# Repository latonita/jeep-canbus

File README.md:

# jeep-canbus   

Projects around CAN BUS in Chrysler Jeep - VES enabler, other small features

PCB for Aux + bluetooth based on xs3868 v3.0 added.

Here is CAN ID map I collected on CAN-B:

# Jeep Grand Cherokee WH 3.0 CRD - CAN-B — complete observed ID/byte map

This is the consolidated byte-level reference for every standard CAN ID that
actually occurs in the captures in this repository. Byte numbering is zero
based. Multi-byte integers are big-endian unless stated otherwise.

Confidence labels:

- **Confirmed** — controlled switch/action test or an unambiguous decode.
- **Probable** — strong behaviour and cross-log evidence; physical identity or
  scale is not completely calibrated.
- **Candidate** — useful working hypothesis that needs an external reference.
- **Unknown** — observed bytes/pattern only; no semantic claim.
- **Static/NM** — constant heartbeat or network-management traffic, not a
  vehicle measurement.

`FF`, a field of all `FF`, or `FFFFFF` frequently means unavailable during
wake-up/key-off. It is not a maximum physical reading.

## Vehicle, controls and measurements

| CAN ID | DLC / period | Byte and bit meaning | Confidence |
|---|---|---|---|
| `000` | 6 / 100 ms | `b0` ignition state: `00` wake/uninitialised, `01` off, `63` ACC, `85` ignition ON/running, `A9` crank. `b1..b5=00`. | **Confirmed** |
| `002` | 8 / 50 ms | `b0:b1` engine RPM, 1 rpm/count. `b2:b3` speed, raw/128 km/h. `b4:b5` wheel/distance pulse counter 1. `b6:b7` counter 2. Counters are rolling unsigned 16-bit values, about 25 counts/m. All `FF` = unavailable/engine off. They are distance pulses, **not wheel angles**. | **Confirmed** |
| `003` | 7 / ~450 ms | `b0` normally `00`; **`bit2`/`+04` = ESP/stability control switched off** (`04 21 80 01 50 FF 00` = Park with ESP off, 2026-10-13 stationary switch test). `b1` unknown (`00/01/05/0D/20/21` observed; constant `21` throughout the 2026-10-13 test). `b2` lever bitfield over a fixed `0x80`: `80=P`, `81=R`, `82=N`, `84=D` — **every AutoStick manual range also reads `84`**, so `b2` alone cannot separate D from a limited range. `b3 bit0` brake switch (`01` for the whole stationary shift test, foot on the brake). `b4` redundant PRNDL and the one byte that resolves the manual ranges — it is the **ASCII code of the character the cluster displays**: `50='P'`, `52='R'`, `4E='N'`, `44='D'`, `34='4'`, `33='3'`, `32='2'`, `31='1'` (AutoStick upper-limit ranges). `b5` normally `FF`. `b6 bit3` 4WD lever pulled; other bits unknown. | Gear/brake/4WD and ESP-off **confirmed**; `b4` ASCII encoding **confirmed**; `b1` unknown |
| `006` | 7 / 100 ms | `b0`: `00` key-off, `18` no indicator, `19` left, `1A` right, `1B` hazard; `38` also observed with an extra unknown bit. `b1..b6` are not decoded; common payloads include `22 04 00 00 02 58`, while the 2026 capture also has different `b1/b3/b4/b5` values. | Indicator byte **confirmed** |
| `013` | 5 / 500 ms | `b0 bit7` data-valid/module-awake; `b0 bit3=1` driver belt unbuckled. `b1=00`. `b2` door-ajar bits: bit0/`01` FL, bit1/`02` FR, bit2/`04` RR, bit3/`08` RL, bit4/`10` hatch; bits add. `b3:b4=49 99`. | **Confirmed** |
| `014` | 7 / 100 ms | `b0:b1:b2` 24-bit odometer, 0.1 km/count; `FFFFFF` unavailable. `b3=FF`. `b4` ambient/outside temperature in °C for the observed positive range: 2026 warm-weather drive `24→25`, older captures mostly `18` (`17–22` total). `b5` and `b6` remain unknown and are **not** validated as fuel level or economy. | Odometer **confirmed**; ambient **probable/high confidence**; `b5..b6` unknown |
| `015` | 6 / 100 ms | `b0` unknown temperature-like channel. `b1` battery/charging voltage in 0.1 V/count: `125` = 12.5 V key-on, `103` = 10.3 V cranking, `143–146` = 14.3–14.6 V running, and `126` = 12.6 V immediately after key-off. `b2` fast air-temperature channel, probably intake/charge air; its observed positive values read plausibly as raw °C, but identity and negative encoding are unconfirmed. `b3=FF`, `b4:b5=00`. | Voltage **confirmed/high confidence**; `b2` candidate; `b0` unknown |
| `01B` | 8 / ~100 ms | `b0` multiplex index `00/01/02`; `b1..b7` are seven ASCII VIN characters for that index. Concatenate the three indexed chunks and discard padding to obtain `1J8HCE8M45Y588369`. Index `03` with zeros appears during boot. | **Confirmed** |
| `02C` | 6 / ~500 ms in 2026 (~600 ms older captures) | `b0` engine-related analog strongly correlated with RPM (`r≈0.95`), possibly oil pressure or load. `b1` coolant temperature, `raw - 40` °C: the 2026 cold drive rises smoothly `68→132` (28→92 °C) in about 10 minutes, then holds `127–131` (87–91 °C); an independent 2015 cold start rises `65–70` to `126–128`. `b2` changing/load-related unknown analog. `b3` normally `64` (occasionally `63`); `b4:b5=00`. All `FF` means unavailable. | Coolant **high confidence**; scale **probable/high confidence**; `b0` candidate; `b2` unknown |
| `0D0` | 2 / ~1.15 s | `b0 bit7`/`+80` **parking brake engaged** — asserted for the first time in the 2026-10-13 stationary test (`04 00` released → `84 00` lever pulled). `b0 bit2`/`+04` was set throughout that session as the released-state baseline, while every 2015 capture reads a flat `00 00`; its meaning is unknown and it is not ESP-off (ESP was on for the `04 00` baseline). `b1=00` always. | Parking brake **confirmed**; `b0 bit2` unknown |
| `11D` | 3 / 100 ms | `b0` switch/button bitfield (`08/10/40` observed); exact button assignments unknown. `b1` small state `0..3`. `b2=00`. | **Unknown switch group** |
| `159` | 6 in every log / ~1 s (2026 drive n=1450: mean 1.0039 s, median 1.000 s, p5 0.998 s, p95 1.001 s; the sole 3.0 s gap is a pre-settling artefact between the first two frames) | `b0=FE` during normal running (100% of the 2026 drive log); power-up/power-down states also carry `00`, `04`, `05`, `0B` or `FF`. `b1:b3=FF FF FF` and DLC 6 are constant in every log in the repo. `b4` is a **validity flag**: `b4=00` ↔ `b5` is a real reading, `b4=01` ↔ `b5=0xFF` (unavailable), true with zero exceptions across every log — confirmed by two live transitions, `playback.log`'s ignition-off (`b4` flips to `01` and the frame settles permanently to `00 FF FF FF 01 FF`) and `radio-ignition-on`'s key-on (`05 FF FF FF 01 FF` → `05 FF FF FF 00 4D` the instant the key reaches ON). `b5` fuel level, probably **litres at 0.5 L/count**: the largest valid raw ever recorded is 154 (77.0 L) against this truck's 77.6 L/20.5 US gal tank — a percentage scale has no reason to stop at 154/255, a litre scale stops exactly where the tank does (`b5×0.5` and `b5/2.0` are the same transform; range alone cannot separate litres from percent, only this ceiling does). 2026 drive raw 138–142 = 69–71 L, logged the morning after a fill and matching the owner's "almost full" (the old `/2.55` percent conversion read the same fill as only 54%); hill trip 140→142 on the slope→138 at home = 70→71→69 L. Cross-check on older captures: raw 25–30 = 12.5–15.0 L (low fuel), raw 77 = 38.5 L (about half), raw 152–154 = 76–77 L (essentially full). Slosh is already heavily damped at the sender: every `b5` change in the 2026 drive is exactly ±1 count (30 changes, largest single step 0.5 L, full-trip peak-to-trough only 4 counts/2.0 L); a consumer could debounce changes shorter than ~10 s to remove the residual flip. Absolute calibration remains open — no brim-to-brim fill has been run against it. | Byte layout (`b4` validity flag, `b0` power-state variability) **confirmed** across every log in the repo; litre scale **probable** (capacity ceiling + owner cross-check), uncalibrated |
| `1A7` | 6 / 100 ms running, ~400 ms key-off | `Q=b0:b1` instantaneous fuel/injection flow; `FFFF` unavailable and zero is valid overrun cut. `b2..b5=00`. Integrate `Q×dt`; do not sum frames or multiply by RPM. Provisional scale: `flow_L/h=Q/160`, so `litres += Q×dt/(160×3600)`. | Rate identity **probable**; divisor 160 candidate |
| `1AC` | 1 / ~950 ms | `b0` dash/dome dimmer-wheel position: `01` top lock (dome on, instruments maximum), `02..08` descending brightness with dome off, `09` bottom lock (dome forced off, minimum). | **Confirmed** |
| `1B2` | 6 / ~1.45 s | `b0 bit7` 4WD lever pulled, causing blinking 4WD telltale/chime. `b1` observed `00/02/07`, probably transfer-case range/status but undecoded. `b2..b5=00`. | Lever bit **confirmed**; `b1` candidate |
| `1B4` | 6 (2953/2953) / 500 ms (mean 502.8 ms, median 500 ms, σ78 ms; 99.83% of gaps 480–520 ms) | `b0` 8-way direction enum: `0=N`, `1=NE`, `2=E`, `3=SE`, `4=S`, `5=SW`, `6=W`, `7=NW`, computed as `round(b1×2/45) mod 8` — sector centres sit at 0/45/90/.../315°, boundaries at 22.5/67.5/.../337.5°. A full 8-phase offset sweep confirms offset 0 with `round` (99.46% agreement, 2937/2953 frames) and rejects `floor` outright (best `floor` phase only 58.35%); independently cross-checked at 99.75% on a 1584-frame 2019 session. The 0.54% of disagreements are all boundary-quantization artifacts (e.g. `b1=146` → 292°, 0.5° shy of the 292.5° boundary, within the ±1° the 2°/count scale allows). `b1` magnetic heading in 2°/count (`0..179` → `0..358°`; observed range this session `0..178`, never reaching the documented 179 ceiling). `b2=07` constant in 2953/2953 frames, likely compass variance-zone/status — only its constancy is established, its meaning is not. `b3..b5=00` constant in 2953/2953 frames. A circular derivative of `b1×2` is only a coarse yaw-rate proxy. | Direction/heading **confirmed** against two independent sessions (2026 n=2953, 2019 n=1584); `b2` constancy **confirmed**, meaning still candidate |
| `1C8` | 1 / 500 ms | `b0` low bits: `00` exterior lights off, `01` position lamps, `02` low beam. Add bit4/`10` for front fog and bit5/`20` for rear fog: e.g. `12` low+front, `32` low+front+rear. | **Confirmed** |
| `210` | 2 / 500 ms | `b0`: `03` lights off, `02` any lights on; `00/01` occur as wake/key-off transients. `b1` instrument-panel dimmer: `00` with lights off; observed/hand-tested ladder `22/44/66/A4/C8`. | **Confirmed**, dimmer ladder one-note caveat |
| `2C0` | 8 / 100 ms | `b0:b1=FF FF`. `b2` accelerator pedal (23 rest, up to 234 floored in old capture). `b3≈b2/2`. `b4` unknown analog, about `7E` at rest. `b5=FF`. `b6` exact mirror of `b2`. `b7` status/validity flags (`02/0E/82/8E/...`). | Pedal **probable/high confidence**; flags unknown |
| `370` | 6 / event-driven | `b0` pulses `01` then `00`, one event per windscreen-wiper sweep. `b1..b5=00`. | **Confirmed** |

## RAR radio/head-unit IDs

The installed head unit is the **RAR radio**. The radio-unplug experiment
confirms that `09F`, `1AB`, `1BB`, `394`, `3D0` and NM node `416` belong to it.

| CAN ID | DLC / period | Byte and bit meaning | Confidence |
|---|---|---|---|
| `09F` | 8 / ~1 s | RAR radio source/current-mode state in `b0..b2`; exact value map incomplete. `b3=00`, `b4:b6=FF FF FF`, `b7=1F`. Closely mirrored by `394`. | Source **confirmed**, value map incomplete |
| `1AB` | 6 / ~3 s | Payload `03 00 00 00 00 00` in observed sessions. Head-unit heartbeat/status; individual semantics unknown. | Head unit **confirmed**; bytes unknown/static |
| `1BB` | 6 / ~1 s | `b0..b5=00` in all captures. Head-unit heartbeat/status. | Head unit **confirmed**; static |
| `394` | 6 / ~1 s | `b0..b2` mirror radio mode/status from `09F`. `b3` button bits: bit0 seek right, bit1 seek left, bit2 fast-forward, bit3 rewind, bit5 random/PTY. b4? `b5=00`. The head unit sends this frame **on press and again on release**, carrying the new state each time (owner, checked against the real unit) — so the ~1 s cadence is the idle heartbeat, not the report rate, and a short tap cannot fall between two frames. **No capture in this repository can confirm any of the bit or byte assignments: `b3`, `b4` and `b5` are all `0x00` in every one of the 5510 `394` frames logged, because nobody has ever pressed one of these buttons while recording.** The row said `b4` until the owner corrected it, and the logs were silent either way. | Byte/bit assignment **owner-stated, unconfirmed by any capture**; press/release behaviour **confirmed** |
| `3D0` | 7 / ~1 s | `b0` volume. `b1` bass, `b2` mid, `b3` treble, `b4` balance, `b5` fade; centre values are commonly around `0A` (fade observed `0C`). `b6=FF`. | **Confirmed/high confidence** |
| `3DD` | 8 / injected command | VES-present announcement to the RAR radio: `b0=03`, `b1..b7=00`. Transmitting `03 00 00 00 00 00 00 00` makes the RAR recognise VES as present and enables its AUX input. This was actively tested, not passively recorded. | **Confirmed by injection test** |

## Static, heartbeat and still-unknown cyclic IDs

These frames are retained because a complete map must show them, but a constant
payload is not proof of a physical meaning.

| CAN ID | DLC / period | Observed bytes | Confidence |
|---|---|---|---|
| `008` | 6 / ~1 s | `00 00 80 80 00 00`. | **Static/unknown** |
| `010` | 8 / ~2 s | Usually `41 01 15 71 63 80 2A 03`; `b0 bit1` participates in a shared alive/toggle burst (`41↔43`). | **Static/unknown** |
| `011` | 8 / ~2 s | Usually `3D 13 00 03 8B 40 00 00`; `b0 bit1` toggles (`3D↔3F`) with several related IDs. | **Static/unknown** |
| `012` | 6 / ~1 s | `b0=00`; `b1=00/10`; `b2=00/02/06`; `b3=40`; `b4:b5=0000/4999`. Possibly security/SKREEM-related, not established. | **Unknown** |
| `02E` | 2 / ~1 s | `1F 00`. | **Static/unknown** |
| `0EC` | 1 / ~1.5 s | `b0=00/01` toggle. | **Unknown** |
| `110` | 8 / ~3 s | Usually `95 7E 04 83 83 00 55 00`; `b0 bit1` toggles (`95↔97`) in the shared burst. | **Static/unknown** |
| `1AD` | 6 / ~2.7 s | Usually `01 42 42 04 01 00`; `b0 bit1` toggles (`01↔03`) in the shared burst. | **Static/unknown** |
| `1AE` | 6 / ~1.4 s | `00 00 00 00 00 00`. | **Static/unknown** |
| `1AF` | 8 / ~2.5 s | Usually `01 E7 00 40 01 A4 08 FF`; `b0 bit1` can toggle (`01↔03`) in the shared burst. | **Static/unknown** |
| `1B0` | 8 / ~5.4 s | `0D DE 03 E8 0A A0 08 DE`. | **Static/unknown** |
| `1B3` | 6 / ~2 s | `00 00 00 00 00 00`. | **Static/unknown** |
| `1B5` | 6 / ~6 s | `FD 0D 17 D1 00 00`. | **Static/unknown** |
| `1B6` | 7 / ~1 s | `00 18 FF 18 FF 18 FF`. | **Static/unknown** |
| `1F8` | 1 / ~2 s | `00`. | **Static/unknown** |
| `3A0` | 2 / 500 ms | `00 00`; heartbeat. | **Static** |
| `3F8` | 6 / 100 ms | `04 00 00 00 00 00`; fast heartbeat/reference frame. | **Static** |

The simultaneous `b0 bit1` changes in `010`, `011`, `110`, `1AD` and `1AF`
strongly suggest a shared transmitter/alive state. They do not establish what
the remaining payload fields mean.

## Rare/event-driven IDs with unknown function

| CAN ID | DLC | Observed bytes/behaviour | Confidence |
|---|---|---|---|
| `1E0` | 6 | Short burst with `b0=01`, ending in `b0=00`; `b1..b5=00`. | **Unknown event** |
| `1E2` | 6 | Rare event; `b0..b2` vary by session (`E4 0D D9`, `05 B7 6B`, `3D B4 65` observed); `b3..b5=00`. | **Unknown event** |
| `3F4` | 6 | Rare burst; `b0..b3` vary by session (`A5 1D E9 37`, `12 60 8F 55`, `28 8A A0 63` observed); `b4:b5=00`. | **Unknown event** |

## OSEK network-management ring

All seven frames have DLC 8 and recur about every 690 ms per node. They are
network management, not vehicle sensor data.

Common layout:

- `b0=FE`: node alive/announcing; `b1` is its own node address.
- `b0=FD`: ring/token data; `b1` is the next node address.
- `b2=3F` normally; bit7 gives `BF`, a sleep indication/request.
- `b3..b7=FF`.

| CAN ID | Node | Normal `FD` successor | Additional observation |
|---|---:|---:|---|
| `400` | `00` | `02` | NM node; module identity unknown. |
| `402` | `02` | `14` | NM node; module identity unknown. |
| `414` | `14` | `15` | NM node; module identity unknown. |
| `415` | `15` | `16` | NM node; module identity unknown. |
| `416` | `16` | `1C` | **RAR head unit/radio**, proven by unplug test. |
| `41C` | `1C` | `1E` | Joins the ring only while ignition is ON. |
| `41E` | `1E` | `00` | Often carries the sleep-indication bit in `b2`. |

The logical ring is `400 → 402 → 414 → 415 → 416 → 41C → 41E → 400`.

## Injected but not passively observed

`3DD` is a **confirmed VES-presence command** with payload
`03 00 00 00 00 00 00 00`: the RAR radio enables AUX when this frame is
transmitted. It never occurs naturally in the repository captures, so it
remains excluded from the 52 passively observed IDs.

## Important absences

- No direct steering-wheel or road-wheel angle has been identified.
- No accelerometer, pitch, roll or high-rate gyro/yaw signal has been identified.
- `1B4 b1` is compass heading and permits only a coarse derived yaw rate.
- `002 b4:b7` are wheel-pulse counters, not wheel angles.
- `1B4` carries no unavailable sentinel and does not stop at key-off: `b1=0xFF`
  is never observed across ~10 log files, and in `playback.log` the frame
  keeps transmitting at its normal cadence with an unchanged, valid heading
  (`06 85 07 00 00 00`, W/266°) straight through the `000` ignition-off
  transition and for ~1000 further lines until the capture ends. Anything
  consuming this must gate key-off on `000` or on bus silence, never on the
  compass frame itself (whether `1B4` eventually goes quiet on true bus sleep
  is unknown — the capture ends mid-stream).
- `159` is the mirror-image case: it does carry a real unavailable sentinel, in `b4`, and consumers must gate on it — `b4=01` means `b5=0xFF` is not a reading (let alone 100% full), true with no exceptions across every log in the repo.
- `1B4` heading is bit-for-bit static when stopped: across all 196
  consecutive stationary (≤2 km/h) sample pairs the 500 ms heading delta was
  exactly 0.0° (mean, median, max and stdev all zero) — no jitter to filter.
  Moving, the median 500 ms delta is 0° and mean |delta| is 1.9°; sustained
  turns run ~18–26°/s, with a genuine peak of 96° in one 500 ms sample
  (192°/s) at a hairpin apex on the hill switchbacks.

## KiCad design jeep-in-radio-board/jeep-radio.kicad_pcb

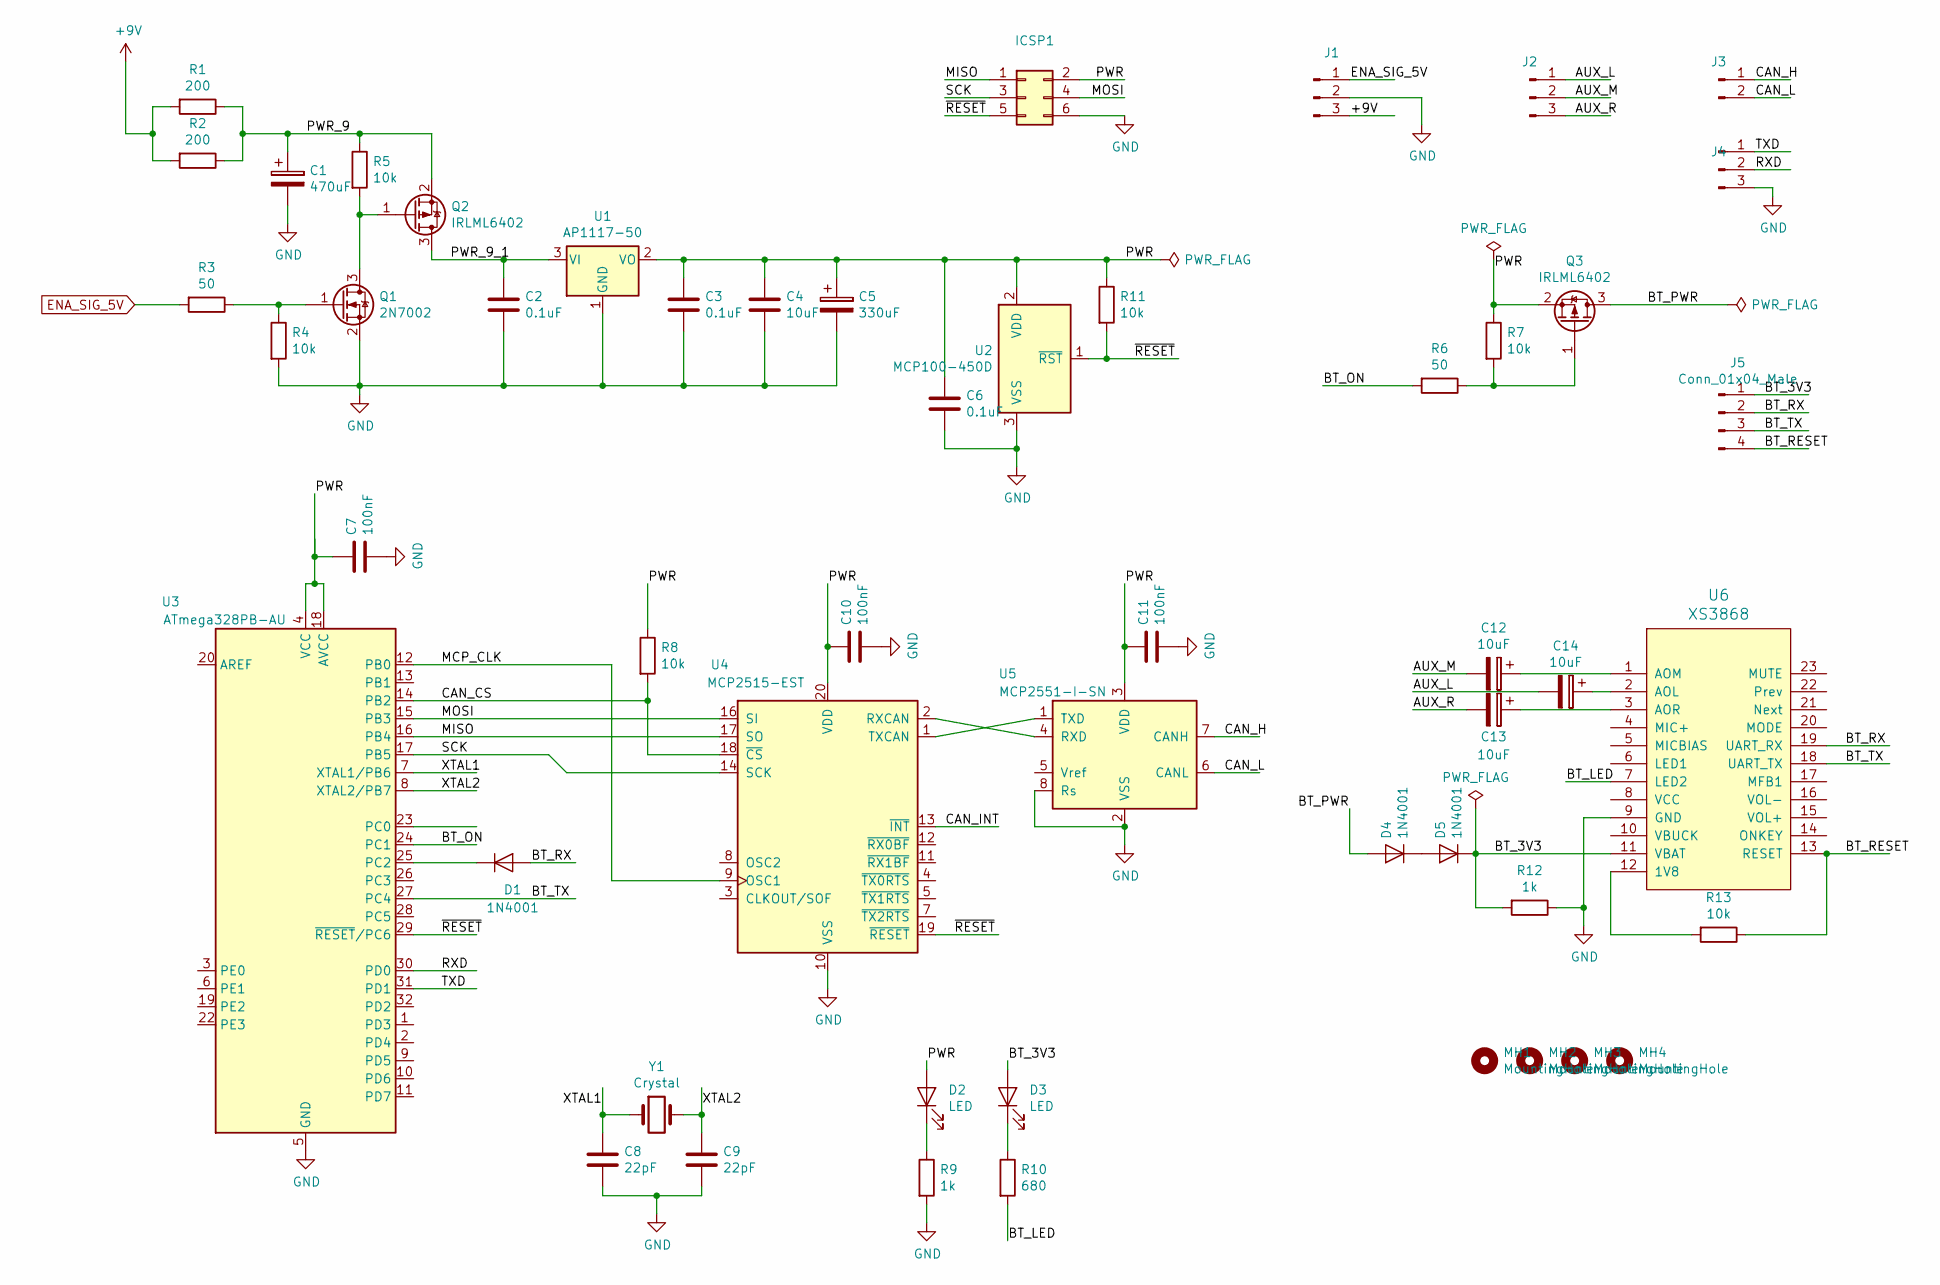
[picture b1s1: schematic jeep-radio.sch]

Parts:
C1: 470uF; CP_Radial_D8.0mm_P3.80mm
C2, C3, C6: 0.1uF; C_0805_2012Metric
C4: 10uF; CP_EIA-3216-18_Kemet-A
C5: 330uF; CP_Radial_D8.0mm_P3.80mm
C7, C10, C11: 100nF; C_0805_2012Metric
C8, C9: 22pF; C_0805_2012Metric
C12, C13, C14: 10uF; C_0805_2012Metric
D1, D4, D5: 1N4001; D_MELF
D2, D3: LED; LED_0603_1608Metric
ICSP1: Conn_02x03_Odd_Even; PinHeader_2x03_P2.54mm_Vertical
J1, J2, J4: Conn_01x03_Male; PinHeader_1x03_P2.54mm_Vertical
J3: Conn_01x02_Male; PinHeader_2x01_P2.54mm_Vertical
J5: Conn_01x04_Male; PinHeader_1x04_P2.54mm_Vertical
MH1, MH2, MH3, MH4: MountingHole; MountingHole_3.2mm_M3_DIN965
Q1: 2N7002; SOT-23
Q2, Q3: IRLML6402; SOT-23
R1, R2: 200; R_1206_3216Metric
R3, R6: 50; R_0805_2012Metric
R4, R5, R7, R8, R11, R13: 10k; R_0805_2012Metric
R9, R12: 1k; R_0805_2012Metric
R10: 680; R_0805_2012Metric
U1: AP1117-50; SOT-223-3_TabPin2
U2: MCP100-450D; SOT-23
U3: ATmega328PB-AU; TQFP-32_7x7mm_P0.8mm
U4: MCP2515-EST; TSSOP-20_4.4x6.5mm_P0.65mm
U5: MCP2551-I-SN; SOIC-8_3.9x4.9mm_P1.27mm
U6: XS3868
Y1: Crystal; Crystal_SMD_HC49-SD

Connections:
+9V: J1.3, R1.2, R2.2
/AUX_L: C14.2, J2.1
/AUX_M: C12.2, J2.2
/AUX_R: C13.2, J2.3
/BT_3V3: D3.2 (A), D5.1 (K), J5.1, R12.2, U6.11 (VBAT)
/BT_LED: R10.2, U6.7 (LED2)
/BT_ON: R6.2, U3.24 (PC1)
/BT_PWR: D4.2 (A), Q3.3 (D)
/BT_RESET: J5.4, R13.1, U6.13 (RESET)
/BT_RX: D1.2 (A), J5.2, U6.19 (UART_RX)
/BT_TX: J5.3, U3.27 (PC4), U6.18 (UART_TX)
/CAN_CS: R8.2, U3.14 (PB2), U4.18 (~CS)
/CAN_H: J3.1, U5.7 (CANH)
/CAN_INT: U4.13 (~INT)
/CAN_L: J3.2, U5.6 (CANL)
/MCP_CLK: U3.12 (PB0), U4.9 (OSC1)
/MISO: ICSP1.1, U3.16 (PB4), U4.17 (SO)
/MOSI: ICSP1.4, U3.15 (PB3), U4.16 (SI)
/PWR: C3.1, C4.1, C5.1, C6.1, C7.1, C10.1, C11.1, D2.2 (A), ICSP1.2, Q3.2 (S), R7.1, R8.1, R11.1, U1.2 (VO), U2.2 (VDD), U3.4 (VCC), U3.18 (AVCC), U4.20 (VDD), U5.3 (VDD)
/PWR_9: C1.1, Q2.2 (S), R1.1, R2.1, R5.1
/PWR_9_1: C2.1, Q2.3 (D), U1.3 (VI)
/RXD: J4.2, U3.30 (PD0)
/SCK: ICSP1.3, U3.17 (PB5), U4.14 (SCK)
/TXD: J4.1, U3.31 (PD1)
/XTAL1: C8.1, U3.7 (XTAL1/PB6), Y1.1
/XTAL2: C9.1, U3.8 (XTAL2/PB7), Y1.2
/~RESET~: ICSP1.5, R11.2, U2.1 (~RST), U3.29 (~RESET~/PC6), U4.19 (~RESET)
ENA_SIG_5V: J1.1, R3.2
GND: C1.2, C2.2, C3.2, C4.2, C5.2, C6.2, C7.2, C8.2, C9.2, C10.2, C11.2, ICSP1.6, J1.2, J4.3, Q1.2 (S), R4.2, R9.2, R12.1, U1.1 (GND), U2.3 (VSS), U3.5 (GND), U3.21 (GND), U4.10 (VSS), U5.2 (VSS), U5.8 (Rs), U6.9 (GND)
unnamed: C12.1, U6.1 (AOM)
unnamed: C13.1, U6.3 (AOR)
unnamed: C14.1, U6.2 (AOL)
unnamed: D1.1 (K), U3.25 (PC2)
unnamed: D2.1 (K), R9.1
unnamed: D3.1 (K), R10.1
unnamed: D4.1 (K), D5.2 (A)
unnamed: Q1.1 (G), R3.1, R4.1
unnamed: Q1.3 (D), Q2.1 (G), R5.2
unnamed: Q3.1 (G), R6.1, R7.2
unnamed: R13.2, U6.12 (1V8)
unnamed: U4.1 (TXCAN), U5.1 (TXD)
unnamed: U4.2 (RXCAN), U5.4 (RXD)

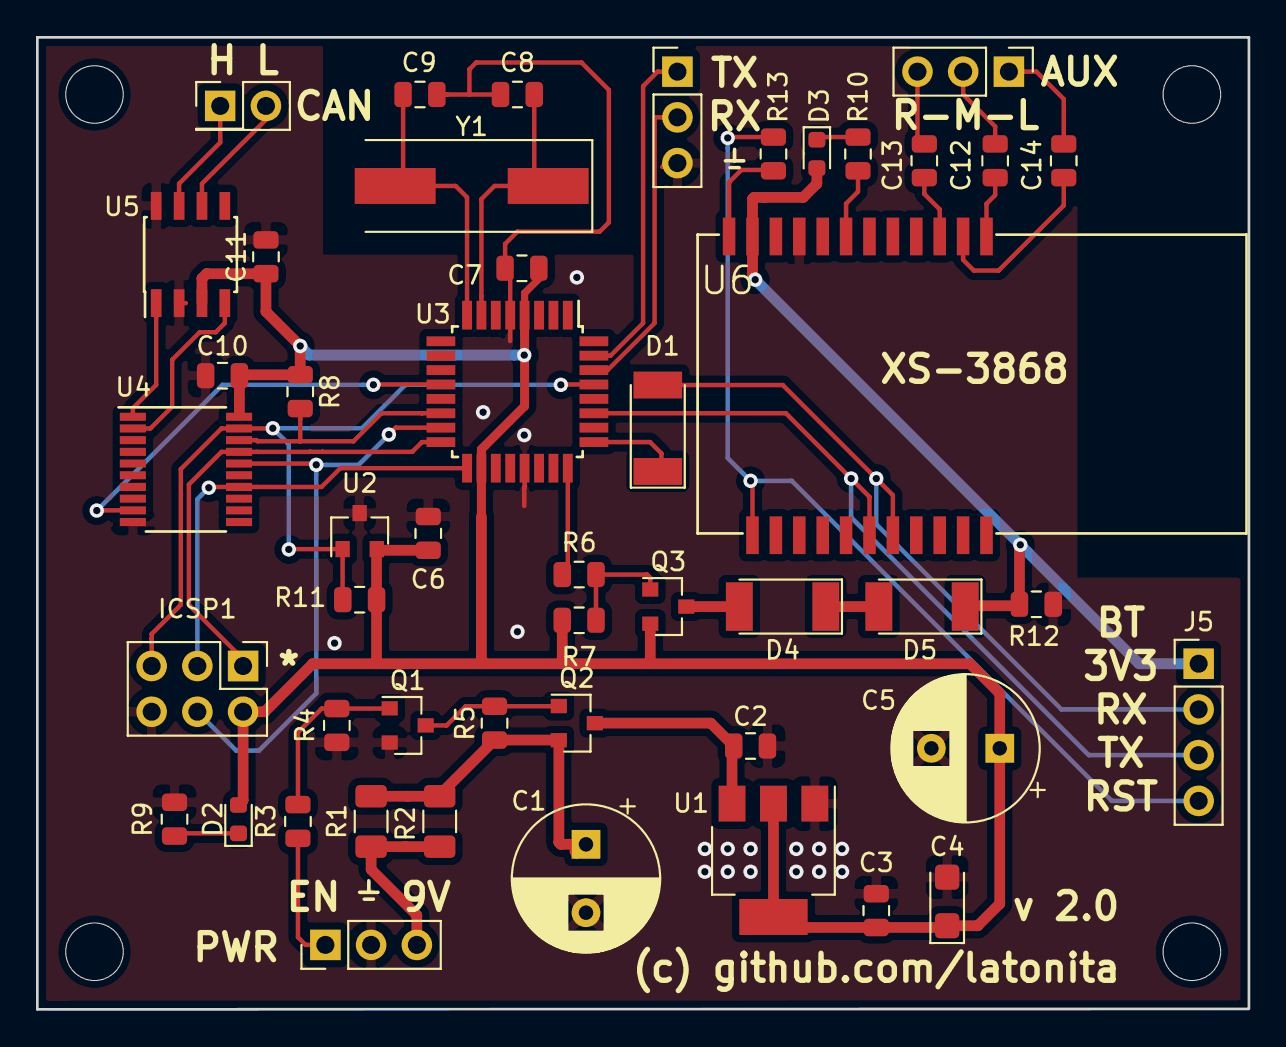
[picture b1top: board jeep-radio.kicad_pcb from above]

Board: 2 copper layers, 67.3 x 54.0 mm, 52 parts (0 on the bottom side), 41 nets.

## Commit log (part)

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2017-04-03 Initial commit - two versions: 1) simple aux enabler; 2) aux + bt control
2017-04-03 Bug fixes + travis.ci
2017-04-03 travis yml fix
2018-09-09 draft
2018-09-10 schematics 0.1
2018-09-10 ver 1
2018-09-10 ver 1.001
2018-11-27 PCB for xs3868v3
2018-11-27 pic of pcb
2019-02-09 pcb to be fixed with new xs3868 footprint
2019-02-10 pcb fix
2019-02-10 pcb fix, sw pins update
2019-02-10 updated gerbers 2.1
